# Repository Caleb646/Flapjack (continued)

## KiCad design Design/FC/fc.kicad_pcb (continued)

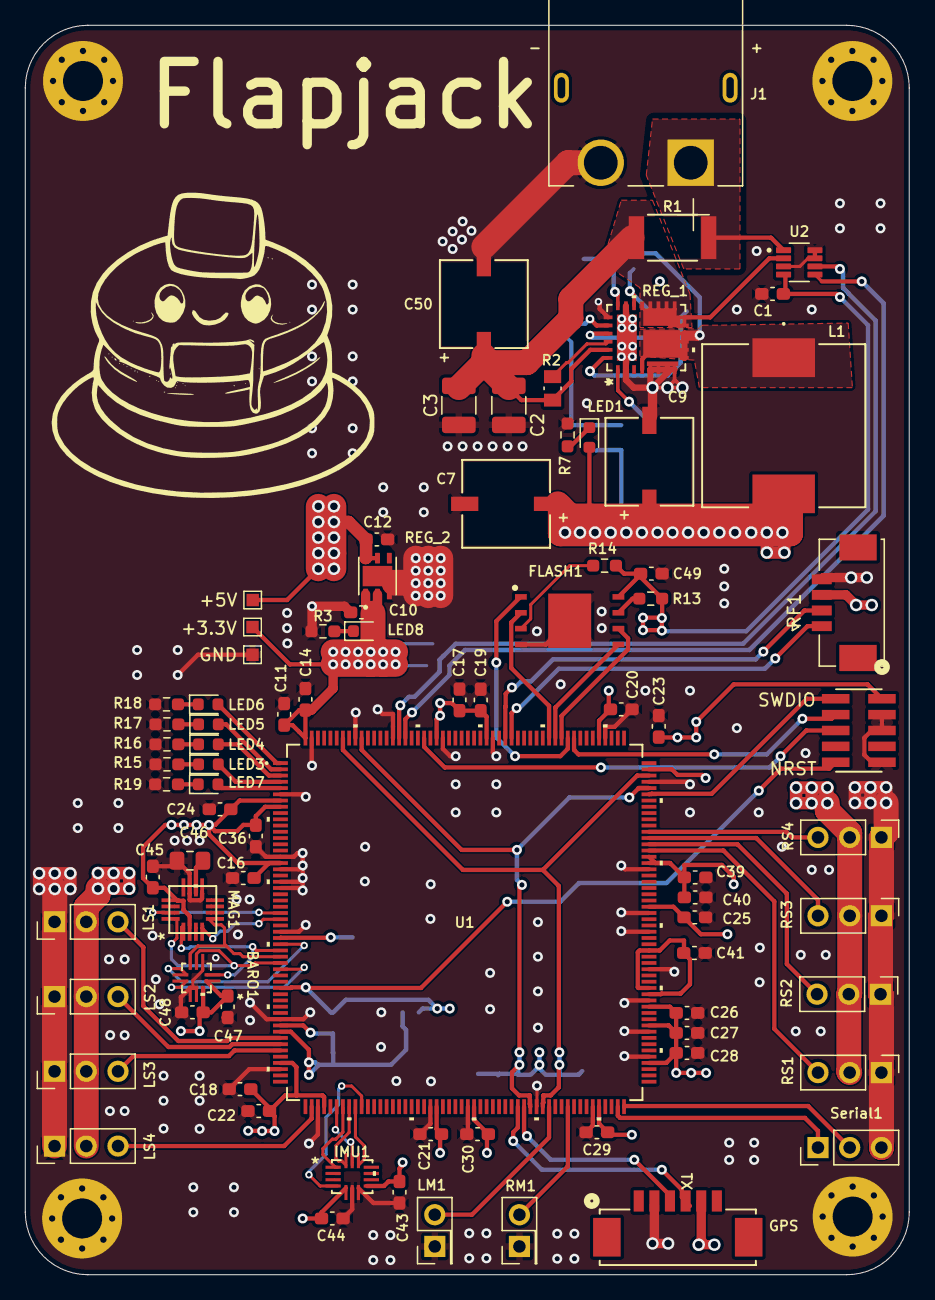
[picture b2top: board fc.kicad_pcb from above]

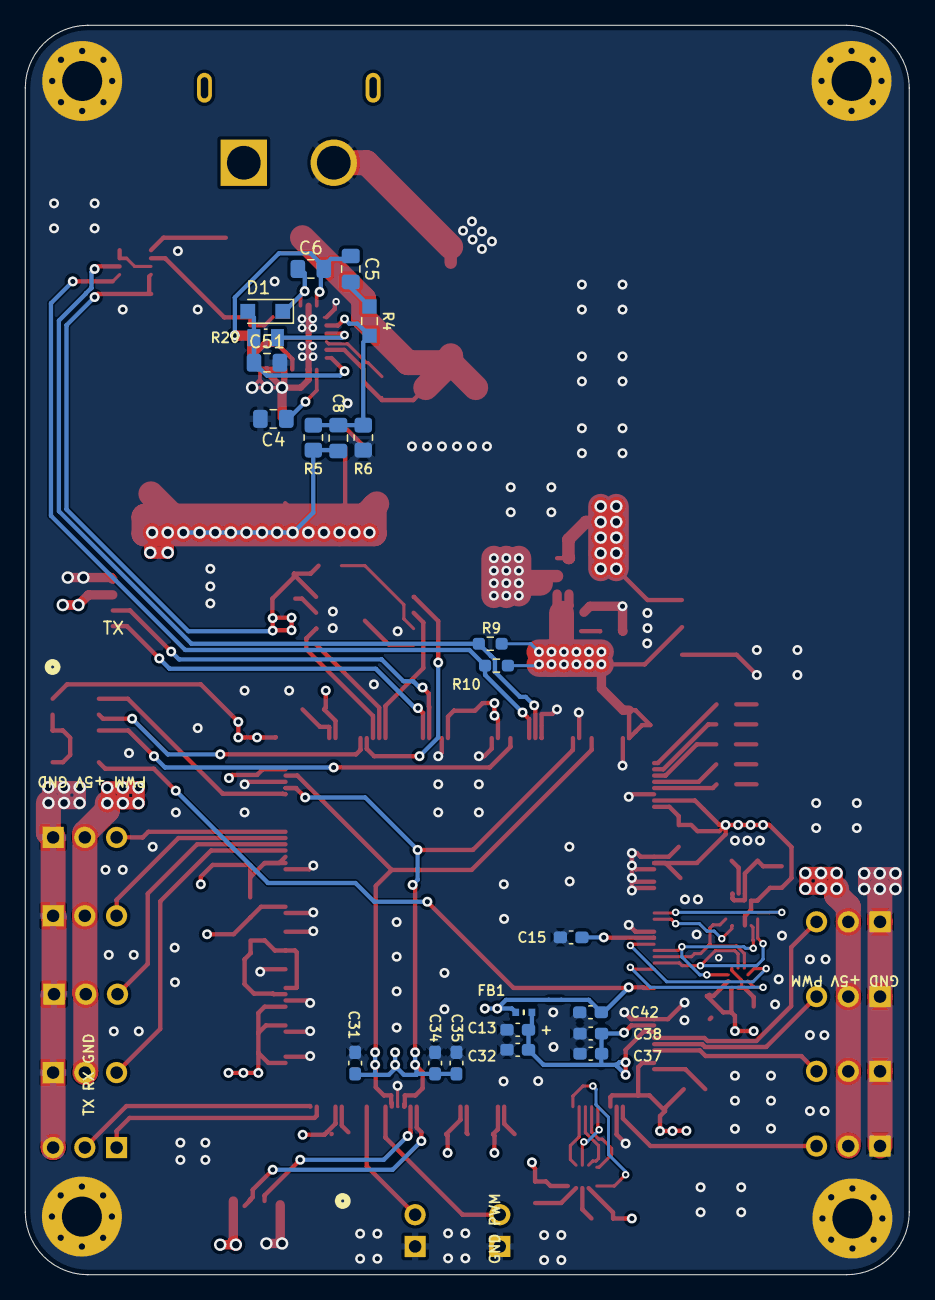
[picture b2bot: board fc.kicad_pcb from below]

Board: 4 copper layers, 70.8 x 100.0 mm, 115 parts (26 on the bottom side), 75 nets.

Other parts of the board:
+3.3V, +5V: TestPoint_Pad_1.0x1.0mm
GND: TestPoint_Pad_1.0x1.0mm

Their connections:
+3.3V: +3.3V.1; also elsewhere on the board
+5V: +5V.1; also elsewhere on the board
GND: GND.1; also elsewhere on the board

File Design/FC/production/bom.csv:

Designator,Footprint,Quantity,Value,LCSC Part #
BARO1,BMP390-10LGA_2X2X0p75_BOS,1,BMP390,
"C1, C14, C15, C16, C17, C18, C19, C20, C21, C22, C23, C24, C25, C26, C27, C28, C29, C30, C32, C36, C37, C39, C40, C42, C43, C44, C47, C48, C49",0603,29,100nF,
"C10, C12",0603,2,10uF,
"C11, C31",0603,2,4.7uF,
"C13, C38, C45",0603,3,1uF,
"C2, C3",1210,2,22uF,
"C34, C35, C41",0603,3,2.2uF,
"C4, C51",0805,2,2.2uF,
C46,0805,1,10uF,
"C5, C6",0805,2,0.1uF,
"C50, C7, C9",CAP_6.3 X 7.7_PAN,3,100uF,
C8,0805,1,4.7nF,
D1,Nexperia_CFP3_SOD-123W,1,SD103AW-TP,
FB1,MPZ1005S121HT000,1,FerriteBead_Small,
FLASH1,W25N01GWZEIG,1,W25N01GWZEIG,
GPS1,CONN_532610001-SD_06Pin_1.25mm,1,Conn_01x06,
IMU1,BMI323_BOS,1,BMI323,
J1,XT60PW-M,1,XT60PW-M,
L1,IND_SRP1265A-6R8M_BRN,1,6.8uH,
"LED1, LED8",0603,2,G,
"LED3, LED7",0603,2,R,
LED4,0603,1,Y,
"LED5, LED6",0603,2,B,
"LM1, RM1",PinHeader_2x01_P2.54mm_Vertical,2,Conn_01x02,
"LS1, LS2, LS3, LS4, RS1, RS2, RS3, RS4, SERIAL1",PinHeader_1x03_P2.54mm_Vertical,9,Conn_01x03,
MAG1,MMC5983MA_MEM,1,MMC5983MA,
R1,RES_PE2512_YAG,1,0.01,
"R10, R9",0603,2,4.7K,
"R13, R14",0603,2,10K,
"R15, R16, R17, R18, R19",0603,5,330,
"R2, R20",RES_ERJ-T06J103V_0805,2,10k,
R3,0603,1,240,
R4,RES_ERJ-PB6B1962V_0805,1,19.6k,
R5,0805,1,6.8K,
R6,0805,1,1.3K,
R7,0603,1,560,
REG_1,MIC26903YJL-TR-MLF28_5X6_MCH,1,MIC26903YJL-TR,
REG_2,SON95P300X300X100-7N,1,LD39200PU33R,
RF1,CONN_532610471_SMD_4Pin_1.25mm,1,Conn_01x04,
SWD1,CONN_GRPB052VWQS-RC_OddEven_2x5Pins_1.27mm,1,Debug_10_1.27,
U1,STM32H747BIT6-LQFP-208,1,STM32H747BIT6,
U2,INA219AIDCNT-SOT65P280X145-8N,1,INA219AIDCNT,

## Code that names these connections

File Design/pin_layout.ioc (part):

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Mcu.Name=STM32H747BITx
Mcu.Package=LQFP208
Mcu.UserName=STM32H747BITx
PA0.GPIOParameters=PinAttribute
PA0.PinAttribute=CortexM7
PA0.Signal=S_TIM5_CH1
PA1.GPIOParameters=PinAttribute
PA1.PinAttribute=CortexM7
PA1.Signal=S_TIM5_CH2
PA13\ (JTMS/SWDIO).GPIOParameters=PinAttribute
PA13\ (JTMS/SWDIO).Mode=Trace_Asynchronous_SW
PA13\ (JTMS/SWDIO).PinAttribute=CortexM7
PA13\ (JTMS/SWDIO).Signal=DEBUG_JTMS-SWDIO
PA14\ (JTCK/SWCLK).GPIOParameters=PinAttribute
PA14\ (JTCK/SWCLK).Mode=Trace_Asynchronous_SW
PA14\ (JTCK/SWCLK).PinAttribute=CortexM7
PA14\ (JTCK/SWCLK).Signal=DEBUG_JTCK-SWCLK
PA15\ (JTDI).GPIOParameters=PinAttribute
PA15\ (JTDI).Mode=NSS_Signal_Hard_Output
PA15\ (JTDI).PinAttribute=CortexM7
PA15\ (JTDI).Signal=SPI3_NSS
PA2.GPIOParameters=PinAttribute
PA2.PinAttribute=CortexM7
PA2.Signal=S_TIM5_CH3
PA3.GPIOParameters=PinAttribute
PA3.PinAttribute=CortexM7
PA3.Signal=S_TIM5_CH4
PA5.GPIOParameters=PinAttribute
PA5.Mode=Full_Duplex_Master
PA5.PinAttribute=CortexM7
PA5.Signal=SPI1_SCK
PA6.GPIOParameters=PinAttribute
PA6.Mode=Full_Duplex_Master
PA6.PinAttribute=CortexM7
PA6.Signal=SPI1_MISO
PA7.GPIOParameters=PinAttribute
PA7.Mode=Full_Duplex_Master
PA7.PinAttribute=CortexM7
PA7.Signal=SPI1_MOSI
PB14.GPIOParameters=PinAttribute
PB14.Mode=Asynchronous
PB14.PinAttribute=CortexM4
PB14.Signal=USART1_TX
PB15.GPIOParameters=PinAttribute
PB15.Mode=Asynchronous
PB15.PinAttribute=CortexM4
PB15.Signal=USART1_RX
PB3\ (JTDO/TRACESWO).GPIOParameters=PinAttribute
PB3\ (JTDO/TRACESWO).Mode=Trace_Asynchronous_SW
PB3\ (JTDO/TRACESWO).PinAttribute=CortexM7
PB3\ (JTDO/TRACESWO).Signal=DEBUG_JTDO-SWO
PB6.GPIOParameters=PinAttribute
PB6.Mode=I2C
PB6.PinAttribute=CortexM7
PB6.Signal=I2C1_SCL
PB7.GPIOParameters=PinAttribute
PB7.Mode=I2C
PB7.PinAttribute=CortexM7
PB7.Signal=I2C1_SDA
PC10.GPIOParameters=PinAttribute
PC10.Mode=Full_Duplex_Master
PC10.PinAttribute=CortexM7
PC10.Signal=SPI3_SCK
PC11.GPIOParameters=PinAttribute
PC11.Mode=Full_Duplex_Master
PC11.PinAttribute=CortexM7
PC11.Signal=SPI3_MISO
PC12.GPIOParameters=PinAttribute
PC12.Mode=Full_Duplex_Master
PC12.PinAttribute=CortexM7
PC12.Signal=SPI3_MOSI
PC4.GPIOParameters=PinAttribute
PC4.PinAttribute=Free
PC4.Signal=GPIO_Output
PC5.GPIOParameters=PinAttribute
PC5.PinAttribute=Free
PC5.Signal=GPXTI5
PC6.GPIOParameters=PinAttribute
PC6.PinAttribute=CortexM7
PC6.Signal=S_TIM8_CH1
PC7.GPIOParameters=PinAttribute
PC7.PinAttribute=CortexM7
PC7.Signal=S_TIM8_CH2
PC8.GPIOParameters=PinAttribute
PC8.PinAttribute=CortexM7
PC8.Signal=S_TIM8_CH3
PC9.GPIOParameters=PinAttribute
PC9.PinAttribute=CortexM7
PC9.Signal=S_TIM8_CH4
PE2.GPIOParameters=PinAttribute
PE2.PinAttribute=Free
PE2.Signal=GPIO_Output
PE3.GPIOParameters=PinAttribute
PE3.PinAttribute=Free
PE3.Signal=GPIO_Output
PE4.GPIOParameters=PinAttribute
PE4.PinAttribute=Free
PE4.Signal=GPIO_Output
PE5.GPIOParameters=PinAttribute
PE5.PinAttribute=Free
PE5.Signal=GPIO_Output
PE6.GPIOParameters=PinAttribute
PE6.PinAttribute=Free
PE6.Signal=GPIO_Output
PF0.GPIOParameters=PinAttribute
PF0.Mode=I2C
PF0.PinAttribute=CortexM7
PF0.Signal=I2C2_SDA
PF1.GPIOParameters=PinAttribute
PF1.Mode=I2C
PF1.PinAttribute=CortexM7
PF1.Signal=I2C2_SCL
PF10.GPIOParameters=PinAttribute
PF10.PinAttribute=Free
PF10.Signal=GPIO_Output
PF3.GPIOParameters=PinAttribute
PF3.PinAttribute=Free
PF3.Signal=GPXTI3
PF4.GPIOParameters=PinAttribute
PF4.PinAttribute=Free
PF4.Signal=GPIO_Output
PF6.GPIOParameters=PinAttribute
PF6.PinAttribute=Free
PF6.Signal=GPXTI6
PF7.GPIOParameters=PinAttribute
PF7.Mode=Full_Duplex_Master
PF7.PinAttribute=CortexM7
PF7.Signal=SPI5_SCK
PF8.GPIOParameters=PinAttribute
PF8.Mode=Full_Duplex_Master
PF8.PinAttribute=CortexM7
PF8.Signal=SPI5_MISO
PF9.GPIOParameters=PinAttribute
PF9.Mode=Full_Duplex_Master
PF9.PinAttribute=CortexM7
PF9.Signal=SPI5_MOSI
PH6.GPIOParameters=PinAttribute
PH6.PinAttribute=CortexM7
PH6.Signal=S_TIM12_CH1
PH9.GPIOParameters=PinAttribute
PH9.PinAttribute=CortexM7
PH9.Signal=S_TIM12_CH2
RCC.SYSCLKFreq_VALUE=64000000
board=custom

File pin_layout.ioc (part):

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Mcu.Name=STM32H747BITx
Mcu.Package=LQFP208
Mcu.UserName=STM32H747BITx
PA5.GPIOParameters=PinAttribute
PA5.Mode=Full_Duplex_Master
PA5.PinAttribute=CortexM7
PA5.Signal=SPI1_SCK
PA6.GPIOParameters=PinAttribute
PA6.Mode=Full_Duplex_Master
PA6.PinAttribute=CortexM7
PA6.Signal=SPI1_MISO
PA7.GPIOParameters=PinAttribute
PA7.Mode=Full_Duplex_Master
PA7.PinAttribute=CortexM7
PA7.Signal=SPI1_MOSI
PB0.GPIOParameters=PinAttribute
PB0.PinAttribute=Free
PB0.Signal=GPIO_Output
PB10.GPIOParameters=PinAttribute
PB10.Mode=Asynchronous
PB10.PinAttribute=CortexM7
PB10.Signal=USART3_TX
PB11.GPIOParameters=PinAttribute
PB11.Mode=Asynchronous
PB11.PinAttribute=CortexM7
PB11.Signal=USART3_RX
PB14.GPIOParameters=PinAttribute
PB14.Mode=Asynchronous
PB14.PinAttribute=CortexM4
PB14.Signal=USART1_TX
PB15.GPIOParameters=PinAttribute
PB15.Mode=Asynchronous
PB15.PinAttribute=CortexM4
PB15.Signal=USART1_RX
PB6.GPIOParameters=PinAttribute
PB6.Mode=I2C
PB6.PinAttribute=CortexM7
PB6.Signal=I2C1_SCL
PB7.GPIOParameters=PinAttribute
PB7.Mode=I2C
PB7.PinAttribute=CortexM7
PB7.Signal=I2C1_SDA
PC4.GPIOParameters=PinAttribute
PC4.PinAttribute=Free
PC4.Signal=GPIO_Output
PC5.GPIOParameters=PinAttribute
PC5.PinAttribute=Free
PC5.Signal=GPIO_Output
PC6.GPIOParameters=PinAttribute
PC6.PinAttribute=CortexM7
PC6.Signal=S_TIM8_CH1
PC7.GPIOParameters=PinAttribute
PC7.PinAttribute=CortexM7
PC7.Signal=S_TIM8_CH2
PH6.GPIOParameters=PinAttribute
PH6.PinAttribute=CortexM7
PH6.Signal=S_TIM12_CH1
PH9.GPIOParameters=PinAttribute
PH9.PinAttribute=CortexM7
PH9.Signal=S_TIM12_CH2
RCC.SYSCLKFreq_VALUE=64000000
board=custom

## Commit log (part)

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2025-04-02 moved motion control to cm7
2025-04-02 reenabled EXTI interrupts for CM7
2025-04-02 refactored IMU
2025-04-02 filter:
2025-04-02 filter
2025-04-03 refactored
2025-04-03 actuators
2025-04-04 implemented filter
2025-04-05 fixed dual core debug config
2025-04-06 fixed bug with uart on cm4
2025-04-07 refactor
2025-04-08 pwm timers
2025-06-14 added imu soft reset for bmi323
2025-06-15 bmi323
2025-06-16 updated imu api to bmi323
2025-06-16 cleanup
2025-06-16 fixed intellisense
2025-06-16 reformatted with clang format
2025-06-16 make files
2025-06-16 main makefile
2025-06-17 fixed hard coded status values
2025-06-19 added better error reporting for IMU
2025-06-19 added initial setup to main loop
2025-06-20 fixed warnings
2025-06-20 started on makefile
2025-06-21 make file
2025-06-21 makefile for CM4 and CM7
2025-06-21 added clang-tidy to vscode settings.json
2025-06-22 clang tidy and format for windows
2025-06-24 started imu calibration
2025-06-25 added self calibration to imu api
2025-06-25 logging data as json to host
2025-06-25 started adding renode
2025-06-26 renode part 2
2025-06-26 renode
2025-06-27 started adding host tests
2025-06-28 tests for imu api
2025-06-28 imu interrupt working
2025-06-28 GUI now logs to file
2025-06-28 fixed narrowing data type bug in IMUGetConf
2025-06-29 doubled CM7's ring buffer for logging
2025-06-29 fixed bug with sign extension are imu gyro and accel data
2025-06-29 made log level selected on gui
2025-06-29 gave uart to cm4
2025-06-30 added tests for imu api
2025-07-01 started on tests for madgwick filter
2025-07-02 imu logging
2025-07-03 rework pwm, servos and motors
2025-07-04 imu calibration works now
2025-07-06 fixed error with dt not being converted to seconds
2025-07-06 added function to warmup madgwick filter on startup and the gui now creates seperate sessions for each serial connect and disconnect
2025-07-06 fixed bug in IMUPollData where while loop would always hit timeout
2025-07-07 started adding queue
2025-07-07 fixed bug with uart overwritting logs
2025-07-07 partial fix to filter.c and imu.c tests
2025-07-08 readme update
2025-07-08 added init function back
2025-07-08 fixed bug in queue where index wrapping was incorrect
2025-07-09 message
2025-07-10 pwm rewrite
2025-07-10 imu tests
2025-07-10 fixed failing imu tests
2025-07-10 timers
2025-07-12 timer dma
2025-07-13 refactored config argument structs to be passed by value instead of ptr
2025-07-14 dma dshot and actuators
2025-07-15 dma timer
2025-07-15 pwm dma
2025-07-16 timer
2025-07-17 fixed dma ptr error
2025-07-17 cleaned up dma and dshot
2025-07-18 tests for actuators
2025-07-18 dshot
2025-07-22 refactor dma conf
2025-07-27 fixed dshot timing issues
2025-07-27 comments
2025-07-29 started adding control through gui or radio transmitter
2025-07-29 added support for control via an external gui or controller
2025-07-29 added flight control tab to gui
2025-07-29 compiler warnings
2025-07-29 commands can now be sent from gui, processed by cm4, and acted upon by cm7
2025-07-30 doubled baud rate for logging
2025-07-30 refactored logger
2025-07-31 refactored sync
2025-07-31 added static definition for sync irq handler
2025-07-31 refactored and passed tests
2025-07-31 default pid values
2025-07-31 fixed bug in IMUProcessUpdatefromINT
2025-08-02 adding an actuators graph to the gui
2025-08-02 servo mixing
2025-08-03 add command type and op state transition handlers
2025-08-03 added throttle values to conf.h
2025-08-07 added actuator ids
2025-08-07 started refactoring logger
2025-08-07 imu working in prototype
2025-08-08 added blocking logging function
2025-08-08 increased timeout for blocking timeout for logger
2025-08-08 motor is working with prop
2025-08-09 added live configuration for pid and throttle
2025-08-09 macros
2025-08-10 refactored queue, sync, and control
2025-08-11 started fixing tests
2025-08-11 fixed imu tests and bug in imucalibrate
2025-08-12 modified clang-format
2025-08-19 design files
2025-08-19 finished power layout for fc
2025-08-20 started on swd interface
2025-08-20 crlf vs lf for kicad
2025-08-20 updated pin layout for swd
2025-08-20 added debug connector
2025-08-22 continuing to add periphs
2025-08-22 added pull up resistors
2025-08-24 added delaymicroseconds
2025-08-25 refactored pins
2025-08-26 add rf receiver connector
2025-08-26 file cleanup
2025-08-26 cleaned up files
2025-08-27 added flash memory
2025-08-28 started adding footprints and filling out bom
2025-08-29 started laying out voltage regulator
2025-08-31 before shrinking pcb
2025-09-01 finished pcb layout and started on bom
2025-09-02 finished filling out bom
2025-09-02 layout
2025-09-03 edited servo connector layout to support larger connectors
2025-09-04 extended smd pads for lga packages
2025-09-04 updated silkscreen
2025-09-04 silkscreen
2025-09-17 consolidating gpio setup
2025-09-18 changes to gpio setup
2025-09-18 spi refactored
2025-09-19 refactored uart
2025-09-19 timer and dma
2025-09-22 dshot and delay timer
2025-09-23 gpio
2025-09-23 finished gpio
2025-09-24 updated dshot and timer to work with new gpio
2025-09-26 refactoring
2025-09-28 refactored filter
2025-09-30 redoing board devices
2025-09-30 added a bus interface to handle setting up and various busses for devices
2025-10-01 testing
2025-10-02 redoing tests
2025-10-04 added interface for external flash storage
2025-10-05 added gps with parsing
2025-10-05 bus callbacks
2025-10-08 started v2
2025-10-08 added servo and control board power
2025-10-09 started on power pcb
2025-10-09 laying out power board
2025-10-11 mostly finished power board layout
2025-10-14 power board
2025-10-15 editing bom
2025-10-15 added test pads for gps rf and debug
2025-10-16 added symlink to Lib folder
2025-10-16 added flash device
2025-10-20 completed main fc board layout
2025-10-20 fc and power board sent out for assembly
2025-10-25 compiler warnings and removed control.c functionality
2025-10-26 gui fix
2025-10-26 fixed bug in ringbuffer init, shared_mem section is now zeroed before jmping to main, and fixed return value in imu update from polling function
2025-10-28 map file
2025-10-30 script for inspecting shared_mem section
2025-10-31 inspect script
2025-10-31 fixed bug with ringbuff size being initialized incorrectly
2025-11-02 dshot implementation using timer for bb
2025-11-08 added core init to group low level init
2025-11-08 removed unnecessary stm hal init
2025-11-16 VCORE is regulated with LDO instead of SMPS. Remove VCAP connection to 3.3V as VCAP is an output not an input
2025-11-20 adding cmock
2025-11-21 cmock
2025-11-21 cmock now mocks hal files and compiles
2025-11-22 added stm32-cmake
2025-11-22 started moving building system over to cmake
2025-11-24 vscode compiler path and include dirs config file
2025-11-24 added stm32cubeh7
2025-11-25 build.sh install mingw gcc for tests
2025-11-25 added syscalls and scheduler
2025-11-26 scripts
2025-11-28 setup debug config using vscode
2025-11-30 chaos
2025-12-02 started re adding spi interface
2025-12-02 bus cfg
2025-12-03 started adding inertial sensor drivers
2025-12-04 comment
2025-12-08 timers and dma
2025-12-09 motors and timers
2025-12-11 dma and timers
2025-12-12 dma tim
2025-12-15 mixer
2025-12-17 attitude
2025-12-18 tasks
2025-12-22 uart
2025-12-23 uart dma
2026-02-05 removed stm32cmake
2026-02-05 Changed from stm32cubeide build to purely cmake
2026-02-05 removed freertos, the separate main.c for each core, and each core now uses its systick timer now that freertos is gone
2026-02-05 removed main.c, main.h for CM4 and CM7. They now both use a main.c in Common/Src
2026-02-05 removed stm32cubeide settings files and update .vscode/c_cpp_properties.json file with new compiler path and the new include paths
2026-02-05 VCore regulator (SMPS or LDO) is now chosen via a macro defined by the board config
2026-02-05 added clang-tidy and clang-format to the msys2 install in sdk_install.py
2026-02-06 fixed clang-format bug in settings.json for setting the clang-format exe path
2026-02-06 removed remanents of FreeRTOS and the -j flag for cmake builds
2026-02-06 removed hal_msp file for CM4 and added the m4 core to the list of .elfs to be built in the cmake file
2026-02-06 started breaking the TaskMotionControlUpdate into to smaller task that run inside the scheduler
2026-02-07 added a simple scheduler to split tasks across both cores and also split tasks into real time and async
2026-02-07 add svd files for both cores. Can now connect to the nucleo board using openocd and flash firmware. Fixed systemclock config
2026-02-07 simplified spi and imu interface to a config header file. fw_build.py now outputs the cmake configure and build steps to their respective files in the build folder
2026-02-07 split shared_mem section into two separate sections. A data and a bss section. CM7 main now zeros the bss shared mem section and loads the data section from flash into ram
2026-02-08 added dshot implementation that uses timer pwm channels to send dshot bits without using dma
2026-02-09 removed motor and servo ids from ids.h
2026-02-09 Changed motor and servo api to handle all servos and motors. Now the mixer api is used to coordinate between the two groups
2026-02-09 removed old uart implementation. removed most of the board conf device interface
2026-02-10 removed mc.h and mc.c. The pid and filter initialization now happens in the main function before the scheduler is called
2026-02-10 removed fcstate implementation. moved core specific system init to CM4 and CM7 directories
2026-02-11 added a minimal crsf implementation
2026-02-11 added simple remote control interface and added a receiver callback to the uart port
2026-02-12 crsf maps crsf channel data to fc channel range.
2026-02-12 cleaned up most of the compiler warnings. removed bus and old spi implementation
2026-02-13 Removed old conf.h and board.h. Moved peripherals to drivers folder. Removed most of timer interface
2026-02-13 removed old pcb design file. ringbuffer no longer sets the given buffer to 0 during initialization
2026-02-13 added help macros to get board settings. started adding the board file for flapjack_v1 board
2026-02-14 gui was not setting the alpha channel for lines in the 3D viewer
2026-02-14 SysTick_Handler was be excluded from the cm4 by the preprocessor. Uart system init wasn't setting the gpio pins
2026-02-14 removed temporary testing code both main functions
2026-02-15 added ITM config to launch.json and in SerialDebug
2026-02-15 added cmake board file that sets up defines for each board based on the -DBOARD_NAME passed to cmake. LDO or SMPS and HSE or HSI will be used based on board defines.
2026-02-20 started adding a task for logging the imu, pid, and attitude
2026-02-21 added a task to log flight data and task to log a heartbeat
2026-02-22 changed filter api to no longer use a global filter struct
2026-02-22 fixed bug with spi dummy bytes being accounted for incorrectly when reading from the imu
2026-02-22 added irq handlers for used spi interfaces and added uarts 4 and 5
2026-02-23 added isEnabled flag to mag and serial debug api to determine whether the api should be used
2026-03-08 fixed usart1 setup where the incorrect AF id was being used. scale down by 2 APB1 and APB2 clocks if HSI (64MHz) is being used as the clock source to HCLK instead of HSE
2026-05-06 updated install python script
2026-05-07 updated vscode .json files and fw_build.py script to work with the new linux paths
2026-05-09 added graphify, merged build and flash script, and added simple test to run on dev board
2026-05-09 added HIL tests
2026-05-18 added connect_assert_srst to openocd.cfg to force connecting under reset
2026-05-18 dshot hil tests are partially working
2026-05-22 fixed dshot hil tests
2026-05-24 added nanopb
2026-05-24 added protobuf to gui
2026-05-26 added platform init and started adding back FreeRTOS
2026-05-27 updated board.py script
2026-05-27 updated hil test to use platform init
2026-05-29 freertos config
2026-05-30 added umsg
2026-05-30 removed old proto files
2026-05-30 added freertos
2026-05-30 removed freertos submodule from umsg submodule
2026-05-30 added freertos to hil tests
2026-06-15 separated the imu interface into an app and driver layer
2026-06-15 moved sensors to device
2026-06-15 imu and mag
